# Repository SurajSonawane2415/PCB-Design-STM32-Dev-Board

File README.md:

# STM32 Development Board

This is a custom STM32 Development PCB Board with an on-board SPI sensor (TC72).

## Board Images

- **Frontend**

- **Backside**

## About the Project

## Getting Started with a Development Board

### STM32F103C8

- The STM32F103xx medium-density performance line family incorporates the high-performance Arm® Cortex®-M3 32-bit RISC core operating at a 72 MHz frequency, high-speed embedded memories (Flash memory up to 128 Kbytes and SRAM up to 20 Kbytes), and an extensive range of enhanced I/Os and peripherals connected to two APB buses. All devices offer two 12-bit ADCs, three general-purpose 16-bit timers plus one PWM timer, as well as standard and advanced communication interfaces: up to two I2Cs and SPIs, three USARTs, a USB, and a CAN.
- The devices operate from a 2.0 to 3.6 V power supply. They are available in both the –40 to +85°C temperature range and the –40 to +105 °C extended temperature range. A comprehensive set of power-saving mode allows the design of low-power applications. The STM32F103xx medium-density performance line family includes devices in six different package types: from 36 pins to 100 pins. Depending on the device chosen, different sets of peripherals are included, the description below gives an overview of the complete range of peripherals proposed in this family.
- These features make the STM32F103xx medium-density performance line microcontroller family suitable for a wide range of applications such as motor drives, application control, medical and handheld equipment, PC and gaming peripherals, GPS platforms, industrial applications, PLCs, inverters, printers, scanners, alarm systems, video intercoms, and HVACs.

### I²C Bus

- I2C communication is the short form for inter-integrated circuits. It is a communication protocol developed by Philips Semiconductors for the transfer of data between a central processor and multiple ICs on the same circuit board using just two common wires.
- Up to two I²C bus interfaces can operate in multimaster and slave modes. They can support standard and fast modes. They support dual slave addressing (7-bit only) and both 7/10-bit addressing in master mode. A hardware CRC generation/verification is embedded.
- They can be served by DMA and they support SM Bus 2.0/PM Bus.
- The I2C Communication starts when the master initiates the START condition, where the SDA line goes from HIGH to LOW while the SCL line in HIGH. This is followed by a 7-bit slave address and a single bit indicating a read (‘1’) operation or a write (‘0’) operation.

 ### Universal Synchronous/Asynchronous Receiver Transmitter (USART)

- The universal synchronous asynchronous receiver transmitter (USART) offers a flexible means of full-duplex data exchange with external equipment requiring an industry-standard NRZ (Non-Return-To-Zero) asynchronous serial data format. The USART offers a very wide range of baud rates using a fractional baud rate generator. It supports synchronous one-way communication and half-duplex single-wire communication. It also supports the LIN (local interconnection network), Smartcard Protocol and IrDA (infrared data association) SIR ENDEC specifications, and modem operations (CTS/RTS). It allows multiprocessor communication. High-speed data communication is possible by using the DMA for multi-buffer configuration.
- One of the USART interfaces is able to communicate at speeds of up to 4.5 Mbit/s. The other available interfaces communicate at up to 2.25 Mbit/s. They provide hardware management of the CTS and RTS signals, IrDA SIR ENDEC support, are ISO 7816 compliant and have LIN Master/Slave capability. All USART interfaces can be served by the DMA controller.

### Serial Peripheral Interface (SPI)

- Serial Peripheral Interface or SPI is a synchronous serial communication protocol that provides full – duplex communication at very high speeds. Serial Peripheral Interface (SPI) is a master – slave type protocol that provides a simple and low-cost interface between a microcontroller and its peripherals.
- Up to two SPIs are able to communicate up to 18 Mbits/s in slave and master modes in full-duplex and simplex communication modes. The 3-bit prescaler gives 8 master mode frequencies and the frame is configurable to 8 bits or 16 bits. The hardware CRC generation/verification supports basic SD Card/MMC modes.
- Both SPIs can be served by the DMA controller.

## Contributor

- [Purva Yeshi](https://github.com/purviyeshi)
- [Suraj Sonawane](https://github.com/SurajSonawane2415)

## Future Work

- [x] Added firmware features and developed design for commercial use: [USB-OTA-Bootloader-Integrated-Custom-STM-Board](https://github.com/SurajSonawane2415/USB-OTA-Bootloader-Integrated-Custom-STM-Board)

## Acknowledgements and Resources

- [Vishwa VITI](https://vishwaspace.github.io/vishwa-web/) for providing us with required resources and Special thanks to my mentor [Karteek Nayak](https://github.com/Karteek-N) and all the seniors at Vishwa, VJTI for their constant support and guidance throughout the project.
- [KiCAD Tutorials](https://www.youtube.com/playlist?list=PL3bNyZYHcRSUhUXUt51W6nKvxx2ORvUQB)
- [STM32F103C8 Datasheet](https://www.st.com/resource/en/datasheet/stm32f103c8.pdf)

## License

[MIT License](https://opensource.org/license/mit)

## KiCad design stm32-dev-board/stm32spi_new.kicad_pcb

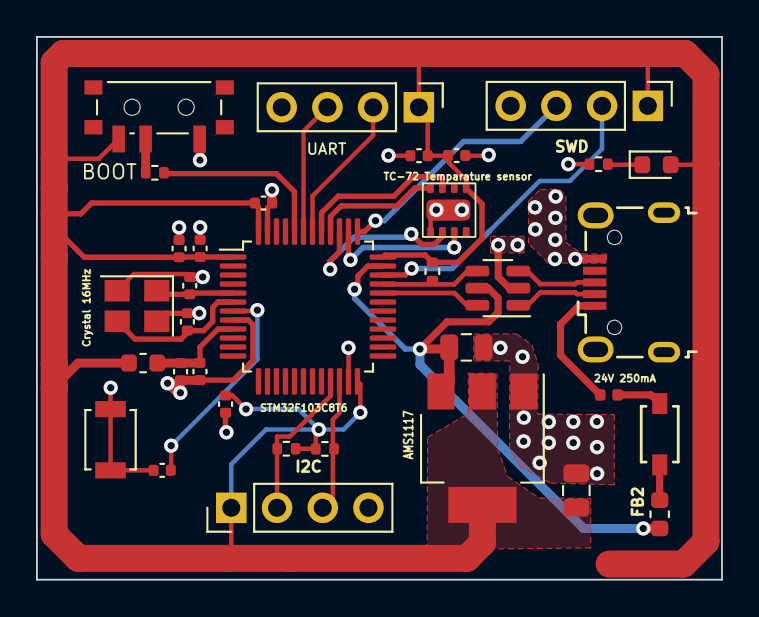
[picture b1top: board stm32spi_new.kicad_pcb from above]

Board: 2 copper layers, 38.1 x 30.2 mm, 34 parts (0 on the bottom side), 26 nets.

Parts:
24V 250mA: 24V 250mA; Fuse_0402_1005Metric
AMS1117: AMS1117-3.3; SOT-223-3_TabPin2
BOOT: SW_SPDT; SW_SPDT_PCM12
C1, C9, C10, C11, C12: 100nf; C_0402_1005Metric
C2, C3: 10pf; C_0402_1005Metric
C4, C5: 22uf; C_0805_2012Metric
C6: 10nf; C_0402_1005Metric
C7, C8: 1uf; C_0402_1005Metric
C13: 10uf; C_0402_1005Metric
CR2: B5819W-TP; SDO_SOD-123_MCC
Crystal 16MHz: 16MHz; Crystal_SMD_3225-4Pin_3.2x2.5mm
D1: LED; LED_0603_1608Metric
FB1, FB2: 120R; L_0603_1608Metric
I2C: Conn_01x04_Male; PinHeader_1x04_P2.54mm_Vertical
J1: USB_B_Micro; USB_Micro-B_Wuerth_629105150521
R: R; R_0402_1005Metric
R1: 10K; R_0402_1005Metric
R2, R3, R4: 1k5; R_0402_1005Metric
STM32F103C8T6: STM32F103C8T6; LQFP-48_7x7mm_P0.5mm
SW1: SW_MEC_5G; SW_SPST_B3U-1000P
SWD: Conn_01x04_Male; PinHeader_1x04_P2.54mm_Vertical
TC-72 Temparature sensor: TC72-DFN
U4: USBLC6-2SC6; SOT-23-6
UART: Conn_01x04_Male; PinHeader_1x04_P2.54mm_Vertical

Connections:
3.3V: AMS1117.2 (VO), BOOT.3 (C), C5.1, C8.1, C9.1, C10.1, C11.1, C12.1, C13.1, D1.2 (A), FB1.2, I2C.1, R.1, R2.1, R4.1, STM32F103C8T6.1 (VBAT), STM32F103C8T6.24 (VDD), STM32F103C8T6.36 (VDD), STM32F103C8T6.48 (VDD), SWD.1, TC-72 Temparature sensor.8 (VDD), UART.1
3.3VA: C6.1, C7.1, FB1.1, STM32F103C8T6.9 (VDDA)
/D+: J1.3 (D+), U4.3 (I/O2)
/D-: J1.2 (D-), U4.1 (I/O1)
/HSE_IN: C2.1, Crystal 16MHz.1, STM32F103C8T6.5 (PD0)
/HSE_OUT: C3.1, Crystal 16MHz.3, STM32F103C8T6.6 (PD1)
/I2C2_SCL: I2C.2, R4.2, STM32F103C8T6.21 (PB10)
/I2C2_SDA: I2C.3, R.2, STM32F103C8T6.22 (PB11)
/NRST: C1.1, STM32F103C8T6.7 (NRST)
/SWCLK: STM32F103C8T6.37 (PA14), SWD.3
/SWDID: STM32F103C8T6.34 (PA13), SWD.2
/USART1_RX: STM32F103C8T6.43 (PB7), UART.3
/USART1_TX: STM32F103C8T6.42 (PB6), UART.2
/USB D+: R2.2, STM32F103C8T6.33 (PA12), U4.4 (I/O2)
/USB D-: STM32F103C8T6.32 (PA11), U4.6 (I/O1)
CE: STM32F103C8T6.38 (PA15), TC-72 Temparature sensor.2 (CE)
GND: AMS1117.1 (GND), BOOT.1 (A), C1.2, C2.2, C3.2, C4.2, C5.2, C6.2, C7.2, C8.2, C9.2, C10.2, C11.2, C12.2, C13.2, Crystal 16MHz.2, Crystal 16MHz.4, I2C.4, J1.5 (GND), R3.2, STM32F103C8T6.8 (VSSA), STM32F103C8T6.23 (VSS), STM32F103C8T6.47 (VSS), SW1.1 (A), SW1.2 (A), SWD.4, TC-72 Temparature sensor.4 (GND), TC-72 Temparature sensor.9 (NC), U4.2 (GND), UART.4
unnamed: CR2.1, FB2.1
unnamed: 24V 250mA.2, CR2.2
unnamed: D1.1 (K), R3.1
unnamed: BOOT.2 (B), R1.1
unnamed: R1.2, STM32F103C8T6.44 (BOOT0)
SCK: STM32F103C8T6.39 (PB3), TC-72 Temparature sensor.3 (SCK)
SDI: STM32F103C8T6.41 (PB5), TC-72 Temparature sensor.6 (SDI)
SDO: STM32F103C8T6.40 (PB4), TC-72 Temparature sensor.5 (SDO)
VBUS: 24V 250mA.1, AMS1117.3 (VI), C4.1, FB2.2, J1.1 (VBUS), STM32F103C8T6.35 (VSS), U4.5 (VBUS)

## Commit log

2024-04-04 add kicad files
2024-04-04 add gerbers
2024-04-04 add documentation
2024-09-16 added future work
